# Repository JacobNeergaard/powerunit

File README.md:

# powerunit
Power distribution unit for race cars

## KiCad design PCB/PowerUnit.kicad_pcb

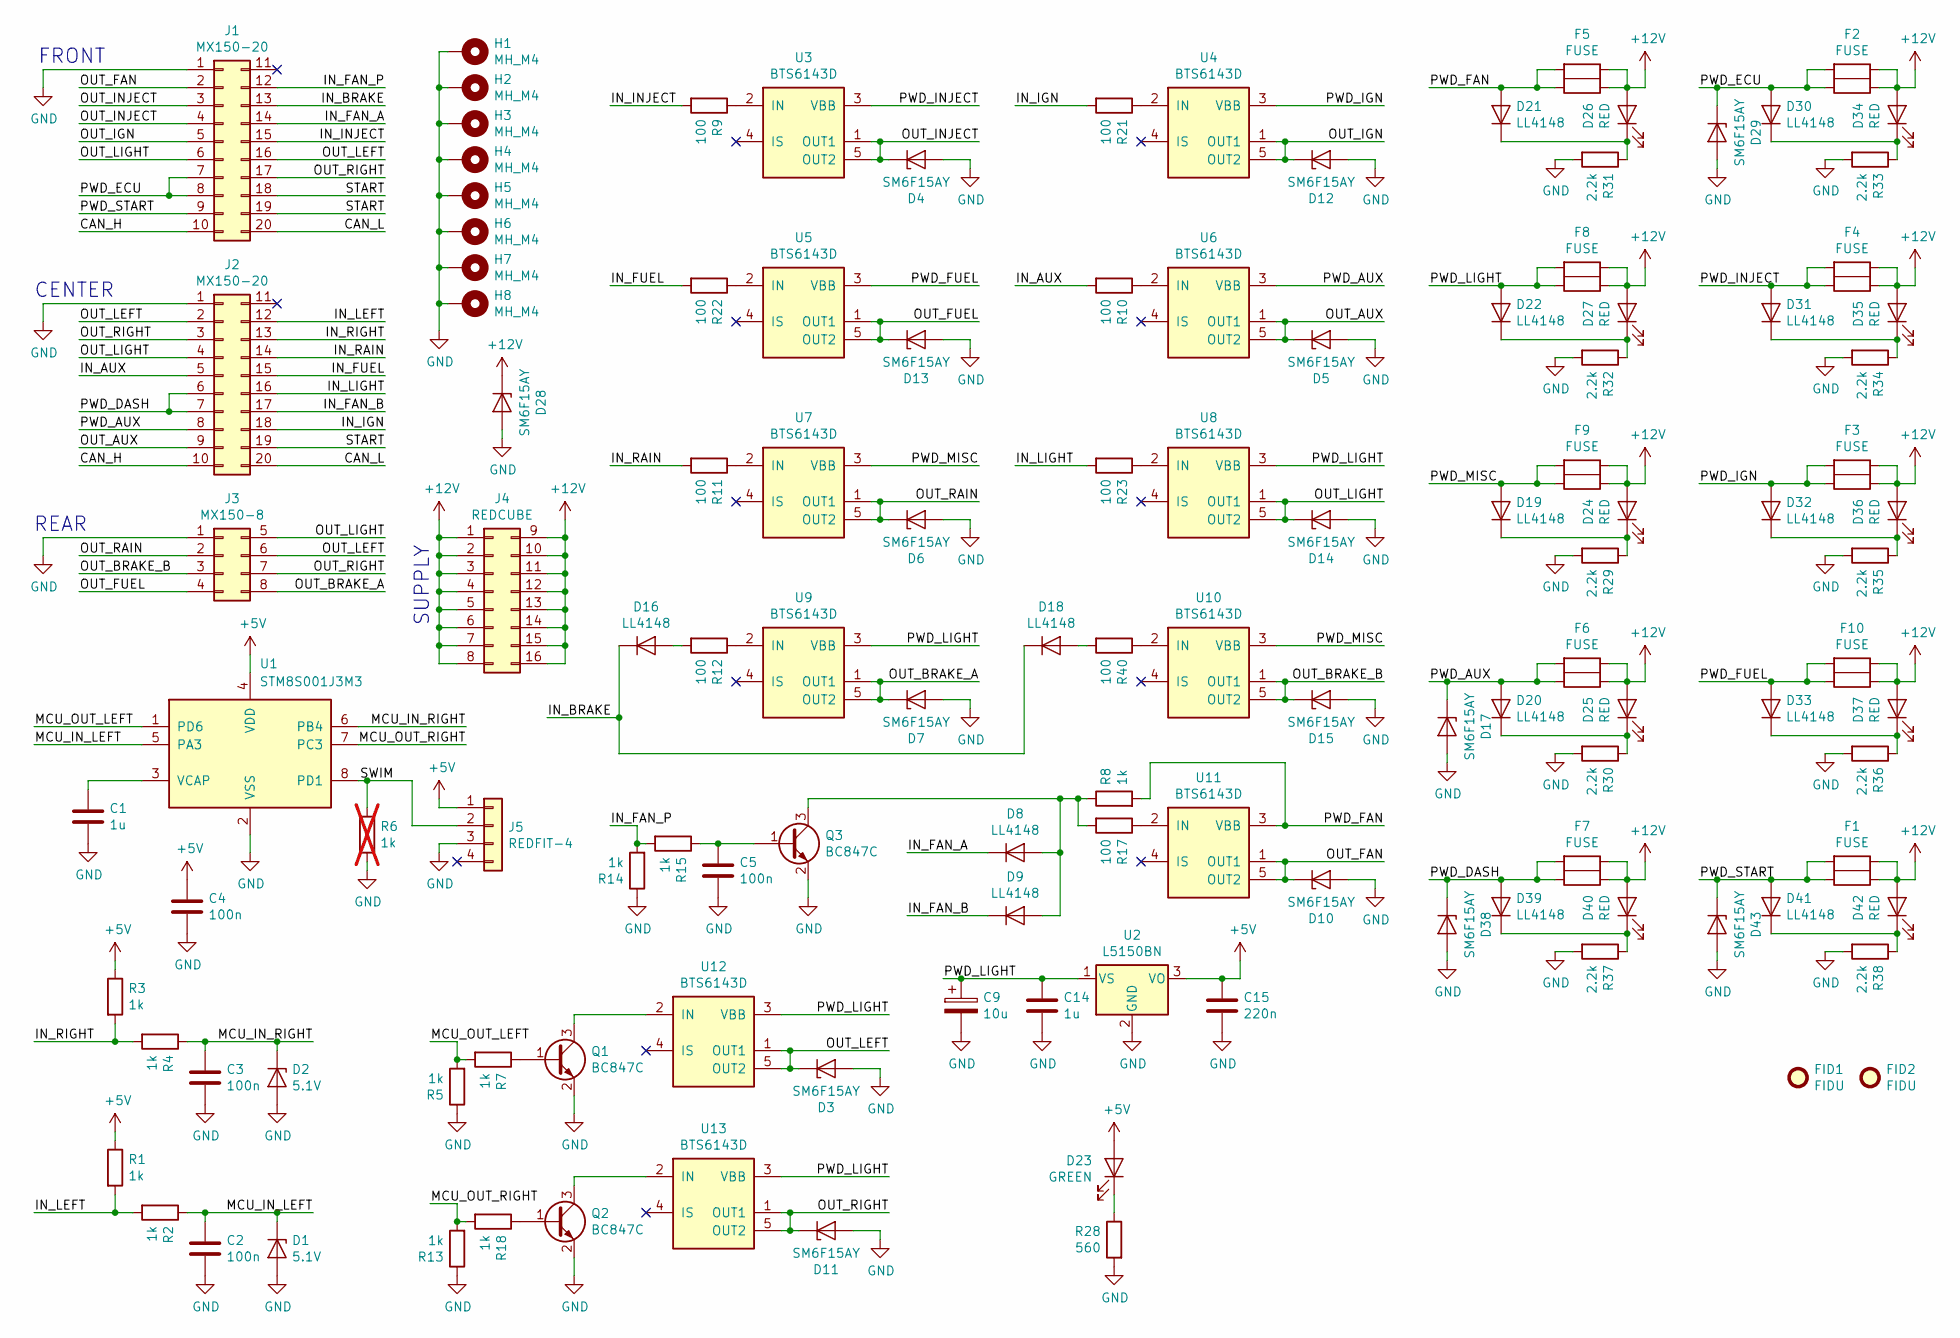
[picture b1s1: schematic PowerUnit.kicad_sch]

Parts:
C1, C14: 1u; C_0805_2012Metric
C2, C3, C4, C5: 100n; C_0805_2012Metric
C9: 10u; CP_EIA-6032-15_Kemet-U
C15: 220n; C_0805_2012Metric
D1, D2: 5.1V; D_MiniMELF
D3, D4, D5, D6, D7, D10, D11, D12, D13, D14, D15, D17, D28, D29, D38, D43: SM6F15AY; D_SOD-128
D8, D9, D16, D18, D19, D20, D21, D22, D30, D31, D32, D33, D39, D41: LL4148; D_MiniMELF
D23: GREEN; LED_0805_2012Metric
D24, D25, D26, D27, D34, D35, D36, D37, D40, D42: RED; LED_0805_2012Metric
F1, F2, F3, F4, F5, F6, F7, F8, F9, F10: FUSE; Keystone_FuseHolder
FID1, FID2: FIDU; Fiducial_1mm_Mask2mm
H1, H2, H3, H4, H5, H6, H7, H8: MH_M4; MountingHole_4.3mm_M4_Pad_Via
J1, J2: MX150-20; Molex_MX150_2x10_Header
J3: MX150-8; Molex_MX150_2x04_Header
J4: REDCUBE; Wurth_WP-BUCF_M6
J5: REDFIT-4; Wurth_WR-WST_IDC_4
Q1, Q2, Q3: BC847C; SOT-23
R1, R2, R3, R4, R5, R7, R8, R13, R14, R15, R18: 1k; R_0805_2012Metric
R6: 1k; R_0805_2012Metric; not fitted
R9, R10, R11, R12, R17, R21, R22, R23, R40: 100; R_0805_2012Metric
R28: 560; R_0805_2012Metric
R29, R30, R31, R32, R33, R34, R35, R36, R37, R38: 2.2k; R_0805_2012Metric
U1: STM8S001J3M3; SOIC-8_3.9x4.9mm_P1.27mm
U2: L5150BN; SOT-223-3_TabPin2
U3, U4, U5, U6, U7, U8, U9, U10, U11, U12, U13: BTS6143D; TO-252-5_TabPin3X

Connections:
+5V: C4.1, C15.1, D23.2 (A), J5.1, R1.1, R3.1, U1.4 (VDD), U2.3 (VO)
+12V: D24.2 (A), D25.2 (A), D26.2 (A), D27.2 (A), D28.1 (K), D34.2 (A), D35.2 (A), D36.2 (A), D37.2 (A), D40.2 (A), D42.2 (A), F1.1A, F1.1B, F2.1A, F2.1B, F3.1A, F3.1B, F4.1A, F4.1B, F5.1A, F5.1B, F6.1A, F6.1B, F7.1A, F7.1B, F8.1A, F8.1B, F9.1A, F9.1B, F10.1A, F10.1B, J4.1, J4.2, J4.3, J4.4, J4.5, J4.6, J4.7, J4.8, J4.9, J4.10, J4.11, J4.12, J4.13, J4.14, J4.15, J4.16
/CAN_H: J1.10, J2.10
/CAN_L: J1.20, J2.20
/IN_AUX: J2.5, R10.2
/IN_BRAKE: D16.1 (K), D18.1 (K), J1.13
/IN_FAN_A: D8.1 (K), J1.14
/IN_FAN_B: D9.1 (K), J2.17
/IN_FAN_P: J1.12, R14.2, R15.2
/IN_FUEL: J2.15, R22.2
/IN_IGN: J2.18, R21.2
/IN_INJECT: J1.15, R9.2
/IN_LEFT: J2.12, R1.2, R2.2
/IN_LIGHT: J2.16, R23.2
/IN_RAIN: J2.14, R11.2
/IN_RIGHT: J2.13, R3.2, R4.2
/MCU_IN_LEFT: C2.1, D1.1 (K), R2.1, U1.5 (PA3)
/MCU_IN_RIGHT: C3.1, D2.1 (K), R4.1, U1.6 (PB4)
/MCU_OUT_LEFT: R5.2, R7.2, U1.1 (PD6)
/MCU_OUT_RIGHT: R13.2, R18.2, U1.7 (PC3)
/OUT_AUX: D5.1 (K), J2.9, U6.1 (OUT1), U6.5 (OUT2)
/OUT_BRAKE_A: D7.1 (K), J3.8, U9.1 (OUT1), U9.5 (OUT2)
/OUT_BRAKE_B: D15.1 (K), J3.3, U10.1 (OUT1), U10.5 (OUT2)
/OUT_FAN: D10.1 (K), J1.2, U11.1 (OUT1), U11.5 (OUT2)
/OUT_FUEL: D13.1 (K), J3.4, U5.1 (OUT1), U5.5 (OUT2)
/OUT_IGN: D12.1 (K), J1.5, U4.1 (OUT1), U4.5 (OUT2)
/OUT_INJECT: D4.1 (K), J1.3, J1.4, U3.1 (OUT1), U3.5 (OUT2)
/OUT_LEFT: D3.1 (K), J1.16, J2.2, J3.6, U12.1 (OUT1), U12.5 (OUT2)
/OUT_LIGHT: D14.1 (K), J1.6, J2.4, J3.5, U8.1 (OUT1), U8.5 (OUT2)
/OUT_RAIN: D6.1 (K), J3.2, U7.1 (OUT1), U7.5 (OUT2)
/OUT_RIGHT: D11.1 (K), J1.17, J2.3, J3.7, U13.1 (OUT1), U13.5 (OUT2)
/PWD_AUX: D17.1 (K), D20.2 (A), F6.2A, F6.2B, J2.8, U6.3 (VBB)
/PWD_DASH: D38.1 (K), D39.2 (A), F7.2A, F7.2B, J2.6, J2.7
/PWD_ECU: D29.1 (K), D30.2 (A), F2.2A, F2.2B, J1.7, J1.8
/PWD_FAN: D21.2 (A), F5.2A, F5.2B, R8.2, U11.3 (VBB)
/PWD_FUEL: D33.2 (A), F10.2A, F10.2B, U5.3 (VBB)
/PWD_IGN: D32.2 (A), F3.2A, F3.2B, U4.3 (VBB)
/PWD_INJECT: D31.2 (A), F4.2A, F4.2B, U3.3 (VBB)
/PWD_LIGHT: C9.1, C14.1, D22.2 (A), F8.2A, F8.2B, U2.1 (VS), U8.3 (VBB), U9.3 (VBB), U12.3 (VBB), U13.3 (VBB)
/PWD_MISC: D19.2 (A), F9.2A, F9.2B, U7.3 (VBB), U10.3 (VBB)
/PWD_START: D41.2 (A), D43.1 (K), F1.2A, F1.2B, J1.9
/START: J1.18, J1.19, J2.19
/SWIM: J5.2, R6.1, U1.8 (PD1)
GND: C1.2, C2.2, C3.2, C4.2, C5.2, C9.2, C14.2, C15.2, D1.2 (A), D2.2 (A), D3.2 (A), D4.2 (A), D5.2 (A), D6.2 (A), D7.2 (A), D10.2 (A), D11.2 (A), D12.2 (A), D13.2 (A), D14.2 (A), D15.2 (A), D17.2 (A), D28.2 (A), D29.2 (A), D38.2 (A), D43.2 (A), H1.1, H2.1, H3.1, H4.1, H5.1, H6.1, H7.1, H8.1, J1.1, J2.1, J3.1, J5.3, Q1.2 (E), Q2.2 (E), Q3.2 (E), R5.1, R6.2, R13.1, R14.1, R28.2, R29.2, R30.2, R31.2, R32.2, R33.2, R34.2, R35.2, R36.2, R37.2, R38.2, U1.2 (VSS), U2.2 (GND)
unnamed: D8.2 (A), D9.2 (A), Q3.3 (C), R8.1, R17.2
unnamed: D16.2 (A), R12.2
unnamed: D18.2 (A), R40.2
unnamed: D19.1 (K), D24.1 (K), R29.1
unnamed: D20.1 (K), D25.1 (K), R30.1
unnamed: D21.1 (K), D26.1 (K), R31.1
unnamed: D22.1 (K), D27.1 (K), R32.1
unnamed: D23.1 (K), R28.1
unnamed: D30.1 (K), D34.1 (K), R33.1
unnamed: D31.1 (K), D35.1 (K), R34.1
unnamed: D32.1 (K), D36.1 (K), R35.1
unnamed: D33.1 (K), D37.1 (K), R36.1
unnamed: D39.1 (K), D40.1 (K), R37.1
unnamed: D41.1 (K), D42.1 (K), R38.1
unnamed: Q1.1 (B), R7.1
unnamed: Q1.3 (C), U12.2 (IN)
unnamed: Q2.1 (B), R18.1
unnamed: Q2.3 (C), U13.2 (IN)
unnamed: C5.1, Q3.1 (B), R15.1
unnamed: C1.1, U1.3 (VCAP)
unnamed: R9.1, U3.2 (IN)
unnamed: R21.1, U4.2 (IN)
unnamed: R22.1, U5.2 (IN)
unnamed: R10.1, U6.2 (IN)
unnamed: R11.1, U7.2 (IN)
unnamed: R23.1, U8.2 (IN)
unnamed: R12.1, U9.2 (IN)
unnamed: R40.1, U10.2 (IN)
unnamed: R17.1, U11.2 (IN)

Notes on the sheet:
SUPPLY
REAR
FRONT
CENTER

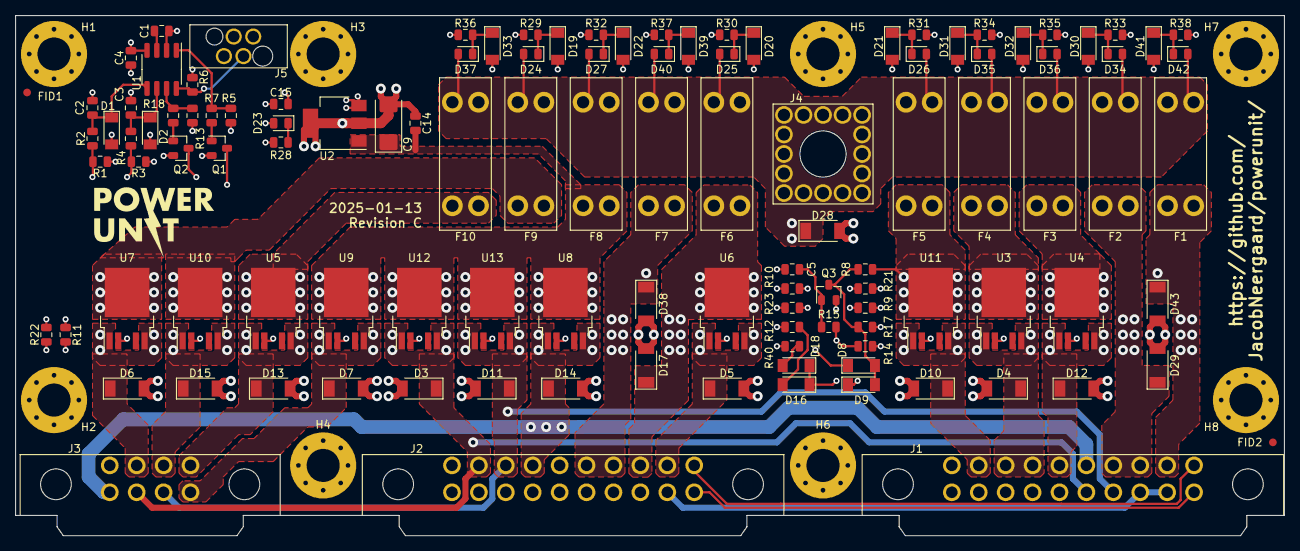
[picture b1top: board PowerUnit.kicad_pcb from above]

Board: 4 copper layers, 165.0 x 67.6 mm, 124 parts (0 on the bottom side), 73 nets.

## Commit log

2019-10-24 first draft
2019-12-02 Correct MCU Ports
2019-12-02 Added PDF and update timestamp
2019-12-02 First Layout added
2019-12-02 added some components
2019-12-02 Added SWIM connector
2019-12-03 Changed TVS diodes
2019-12-04 All footprints added
2019-12-14 First PCB Layout done
2019-12-14 Now with first Gerber
2019-12-15 fix labels
2019-12-15 Fix thermal relief
2019-12-15 Added revision
2020-01-02 fix Fab
2020-01-03 Harness BOM
2020-01-03 Harness BOM update
2020-02-06 Enclosure and logo
2020-02-09 Added STL and SwitchPanel
2020-03-11 Changed debug connector
2020-03-12 updated MCU symbol
2020-04-16 new high-side switch and debugconn
2020-04-24 remove resistors / New layout
2020-04-24 Done RevB
2020-05-02 Updated switch panel
2020-05-13 update enclosure
2020-05-18 Software added
2022-02-20 update with purchase info
2022-02-20 fix CSV file
2022-02-20 Add header
2022-02-20 remove dual FLIGHT connector
2023-03-04 Updated to KiCAD 7.0
2023-03-04 Convert Schematic to KiCAD 7.0
2023-03-04 Remove old KiCAD cache
2023-03-04 Add Fan pull-up
2024-03-31 Clean code a bit
2024-04-01 Remove unused Delay function
2024-12-18 Update 2-pin male part no
2025-01-12 Production data Rev C
2025-01-13 Update Assembly data to Rev C
2025-01-13 Update Silkscreen design

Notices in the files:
PCB/PowerUnit.kicad_pcb:
Apache License 2.0
